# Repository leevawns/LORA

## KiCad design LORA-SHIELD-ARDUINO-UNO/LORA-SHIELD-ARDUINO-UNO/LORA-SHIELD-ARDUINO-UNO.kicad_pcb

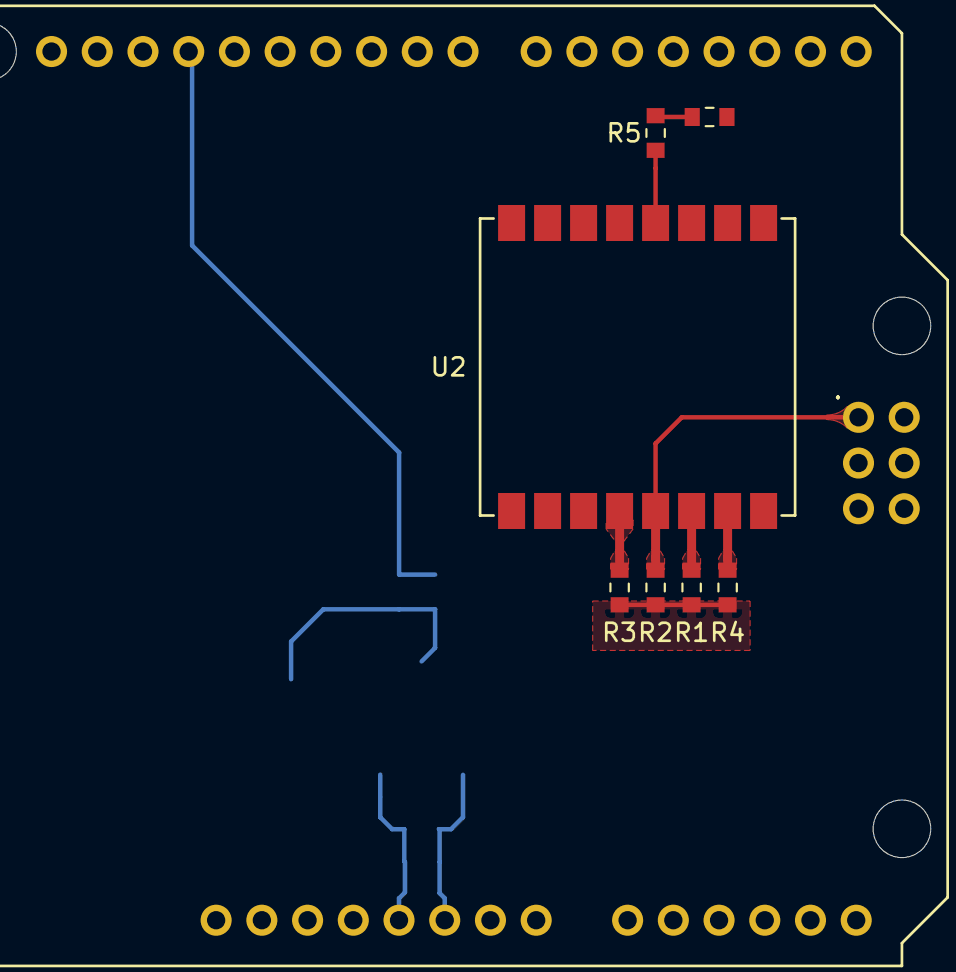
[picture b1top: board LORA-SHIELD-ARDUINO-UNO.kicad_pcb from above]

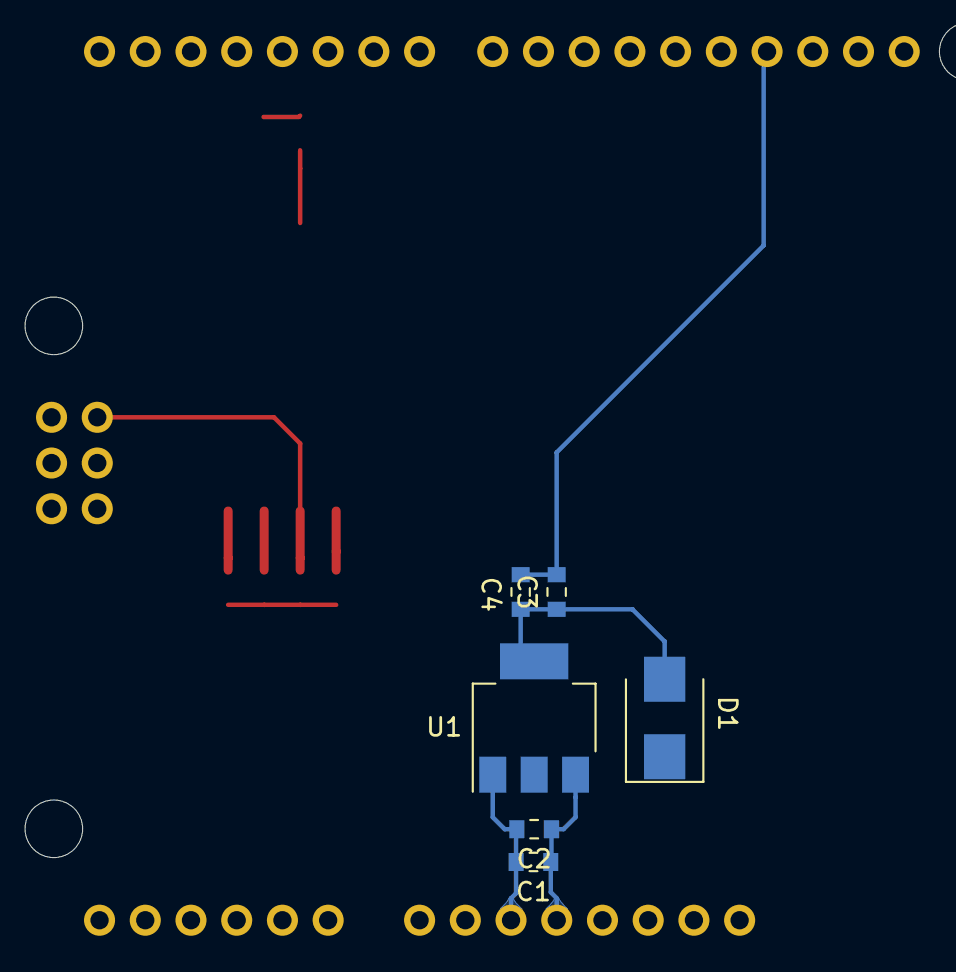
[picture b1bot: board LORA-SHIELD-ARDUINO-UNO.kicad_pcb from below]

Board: 2 copper layers, 14 parts (6 on the bottom side), 10 nets.

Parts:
C1, C4: 10u; C_0603_1608Metric_Pad0.84x1.00mm_HandSolder
C2, C3, C5: 100n; C_0603_1608Metric_Pad0.84x1.00mm_HandSolder
D1: D_ALT; D_SMB
R1, R2, R3, R4, R5: 10k; R_0603_1608Metric_Pad0.84x1.00mm_HandSolder
U1: AZ1117-3.3; SOT-223-3_TabPin2
U2: Ai-Thinker-Ra-01; Ai-Thinker-Ra-01-LoRa
XA1: Arduino_Uno_Shield

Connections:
+3V3: C3.1, C4.1, C5.1, D1.2, R1.1, R2.1, R3.1, R4.1, R5.1, U1.2, U2.3
+5V: C1.1, C2.1, D1.1, U1.3, XA1.5V1, XA1.5V2
GNDA: C1.2, C2.2, C3.2, C4.2, U1.1, XA1.GND1, XA1.GND2, XA1.GND3, XA1.GND4
IRQ: U2.5, XA1.D2
MISO: R2.2, U2.13, XA1.MISO
MOSI: R1.2, U2.14, XA1.MOSI
unnamed: U2.2, U2.9, U2.16
RS: R5.2, U2.4, XA1.D9
SC: R4.2, U2.15, XA1.D10
SCK: R3.2, U2.12, XA1.SCK

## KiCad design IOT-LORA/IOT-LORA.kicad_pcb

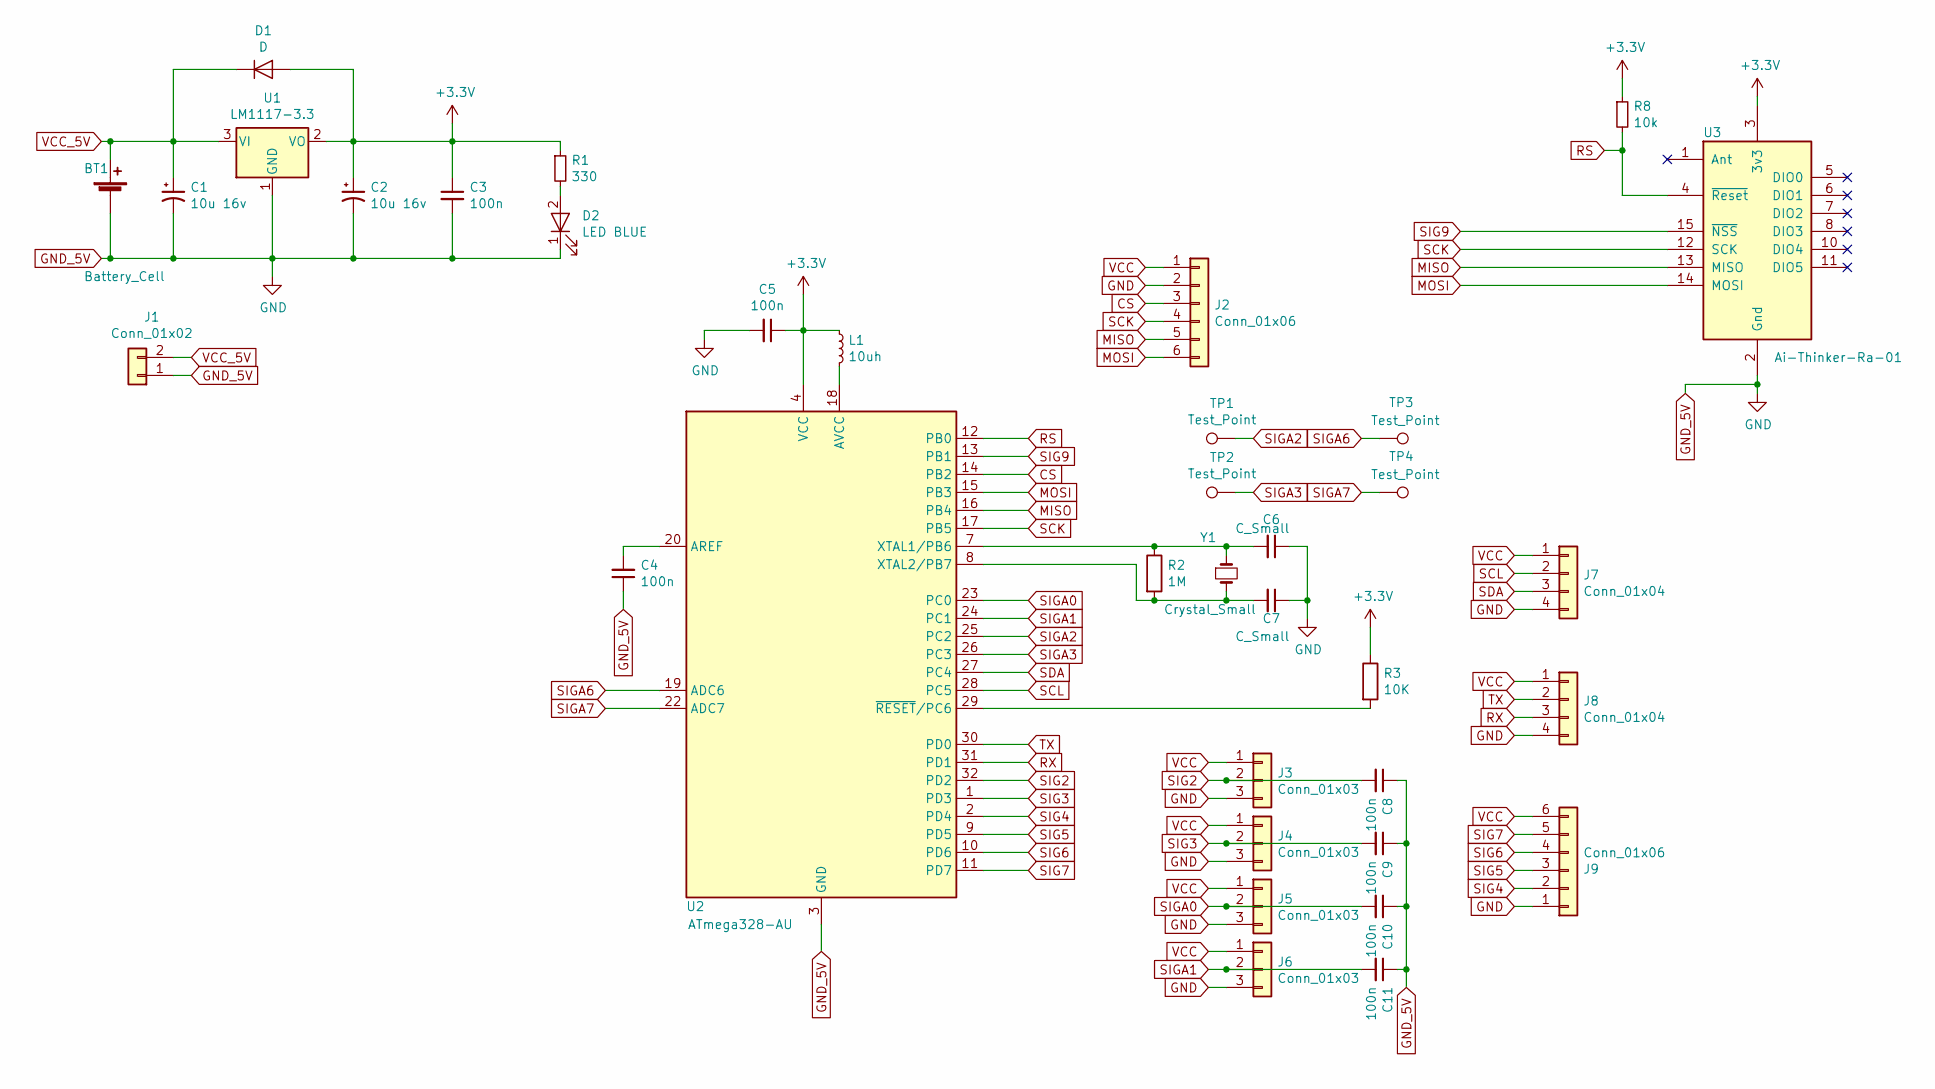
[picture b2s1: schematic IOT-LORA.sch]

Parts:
BT1: Battery_Cell; BatteryHolder_MPD_BH-18650-PC2
C1, C2: 10u 16v; CP_Elec_4x5.3
C3, C4, C5, C8, C9, C10, C11: 100n; C_0805_2012Metric_Pad1.15x1.50mm_HandSolder
C6, C7: C_Small; C_0805_2012Metric_Pad1.15x1.50mm_HandSolder
D1: D; D_SMA
D2: LED BLUE; LED_0805_2012Metric_Pad0.97x1.50mm_HandSolder
J1: Conn_01x02; JST_XH_B02B-XH-A_1x02_P2.50mm_Vertical
J2, J9: Conn_01x06; JST_XH_B06B-XH-A_1x06_P2.50mm_Vertical
J3, J4, J5, J6: Conn_01x03; JST_XH_B03B-XH-A_1x03_P2.50mm_Vertical
J7, J8: Conn_01x04; JST_XH_B04B-XH-A_1x04_P2.50mm_Vertical
L1: 10uh; L_0805_2012Metric_Pad1.15x1.50mm_HandSolder
R1: 330; R_0805_2012Metric_Pad1.15x1.50mm_HandSolder
R2: 1M; R_0603_1608Metric_Pad0.84x1.00mm_HandSolder
R3: 10K; R_0805_2012Metric_Pad1.15x1.50mm_HandSolder
R8: 10k; R_0805_2012Metric_Pad1.15x1.50mm_HandSolder
TP1, TP2, TP3, TP4: Test_Point; TestPoint_Pad_D1.0mm
U1: LM1117-3.3; SOT-223-3_TabPin2
U2: ATmega328-AU; TQFP-32_7x7mm_P0.8mm
U3: Ai-Thinker-Ra-01; Ai-Thinker-Ra-01-LoRa
Y1: Crystal_Small; Crystal_SMD_HC49-SD_HandSoldering

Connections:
+3V3: C2.1, C3.1, C5.1, D1.2 (A), L1.1, R1.1, R3.1, R8.1, U1.2 (VO), U2.4 (VCC), U2.6 (VCC), U3.3 (3v3)
CS: J2.3, U2.14 (PB2)
GND: J2.2, J3.3, J4.3, J5.3, J6.3, J7.4, J8.4, J9.1
MISO: J2.5, U2.16 (PB4), U3.13 (MISO)
MOSI: J2.6, U2.15 (PB3), U3.14 (MOSI)
unnamed: C4.2, U2.20 (AREF)
unnamed: C6.2, R2.1, U2.7 (XTAL1/PB6), Y1.1
unnamed: C7.2, R2.2, U2.8 (XTAL2/PB7), Y1.2
unnamed: D2.2 (A), R1.2
unnamed: L1.2, U2.18 (AVCC)
unnamed: R3.2, U2.29 (~RESET~/PC6)
RS: R8.2, U2.12 (PB0), U3.4 (~Reset)
RX: J8.3, U2.31 (PD1)
SCK: J2.4, U2.17 (PB5), U3.12 (SCK)
SCL: J7.2, U2.28 (PC5)
SDA: J7.3, U2.27 (PC4)
SIG2: C8.2, J3.2, U2.32 (PD2)
SIG3: C9.2, J4.2, U2.1 (PD3)
SIG4: J9.2, U2.2 (PD4)
SIG5: J9.3, U2.9 (PD5)
SIG6: J9.4, U2.10 (PD6)
SIG7: J9.5, U2.11 (PD7)
SIG9: U2.13 (PB1), U3.15 (~NSS)
SIGA0: C10.2, J5.2, U2.23 (PC0)
SIGA1: C11.2, J6.2, U2.24 (PC1)
SIGA2: TP1.1, U2.25 (PC2)
SIGA3: TP2.1, U2.26 (PC3)
SIGA6: TP3.1, U2.19 (ADC6)
SIGA7: TP4.1, U2.22 (ADC7)
TX: J8.2, U2.30 (PD0)
VCC: J2.1, J3.1, J4.1, J5.1, J6.1, J7.1, J8.1, J9.6
VCC_5V: BT1.1 (+), C1.1, D1.1 (K), J1.2, U1.3 (VI)

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
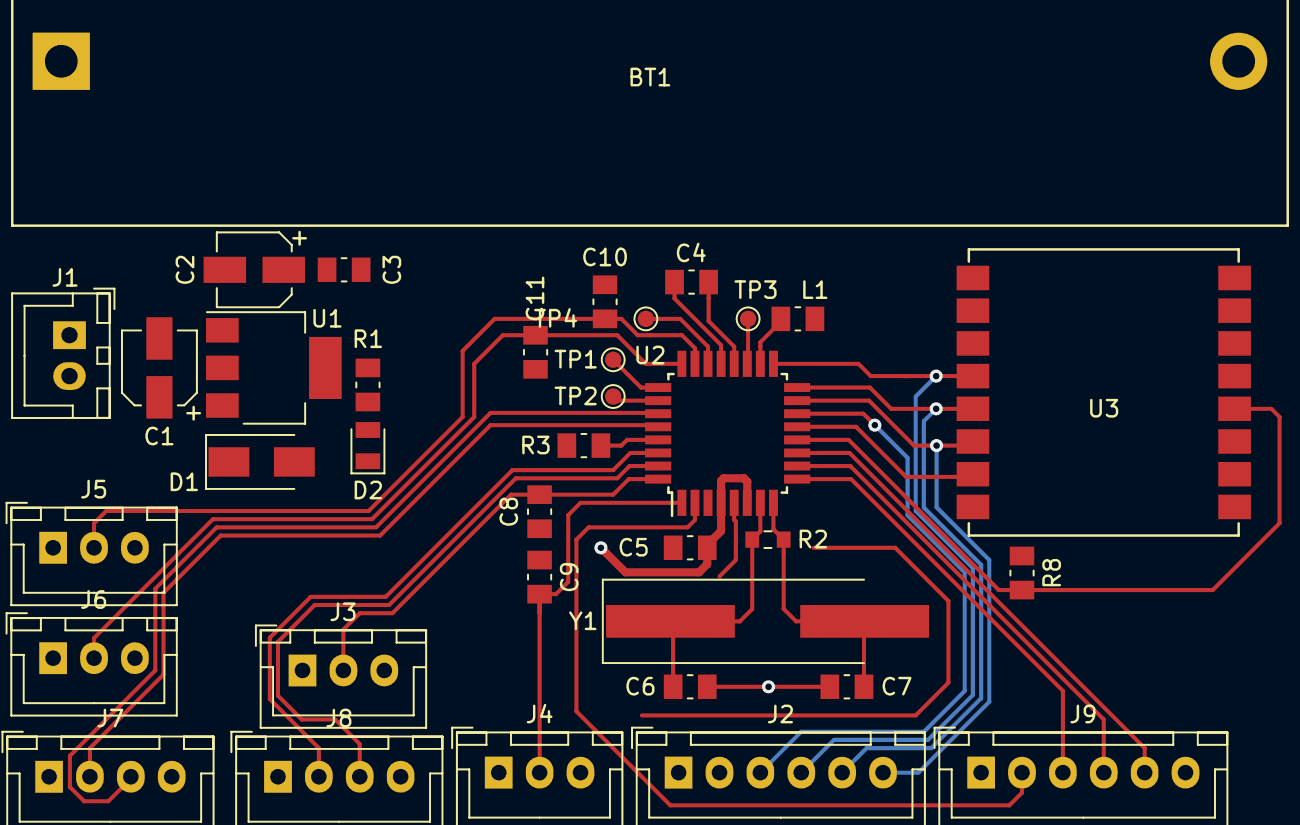
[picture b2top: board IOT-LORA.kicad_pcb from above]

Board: 2 copper layers, 36 parts (0 on the bottom side), 34 nets.

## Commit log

2018-10-29 initial project iot lora
2019-06-28 modifier
